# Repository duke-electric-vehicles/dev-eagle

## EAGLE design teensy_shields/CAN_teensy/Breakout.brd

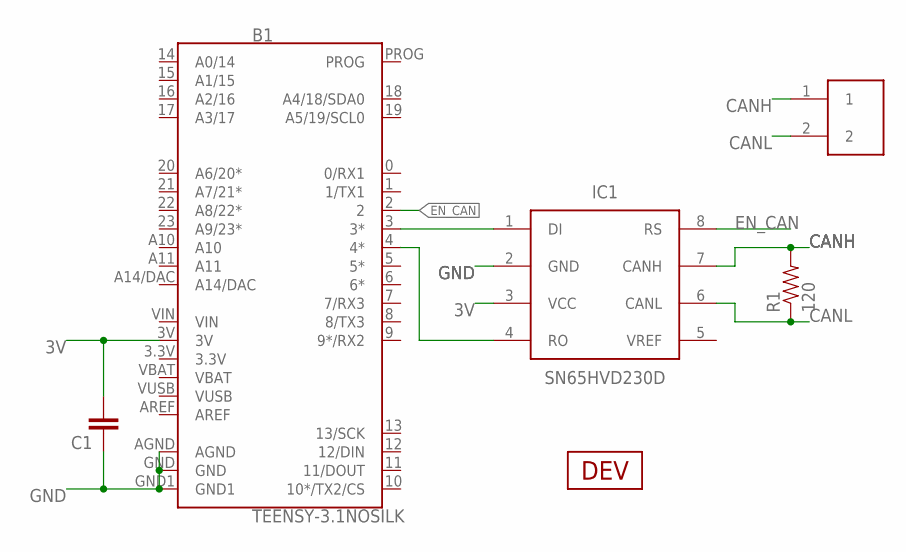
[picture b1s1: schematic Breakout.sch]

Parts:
B1: TEENSY-3.1NOSILK; TEENSY-3.1_NOSILK
C1: CAP0603-CAP; 0603-CAP
IC1: SN65HVD230D; SO-8
R1: 120; 0603-RES
U$1: HEADER2; 2PINVALULOK
U$2: DEV

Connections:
3V: B1.3.3V, B1.3V, C1.2, IC1.3 (VCC)
CANH: IC1.7 (CANH), R1.2, U$1.1
CANL: IC1.6 (CANL), R1.1, U$1.2
EN_CAN: B1.2, IC1.8 (RS)
GND: B1.AGND, B1.GND, B1.GND1, C1.1, IC1.2 (GND)
unnamed: B1.3 (3*), IC1.1 (DI)
unnamed: B1.4 (4*), IC1.4 (RO)
VBAT: B1.VBAT
VIN: B1.VIN
VUSB: B1.VUSB

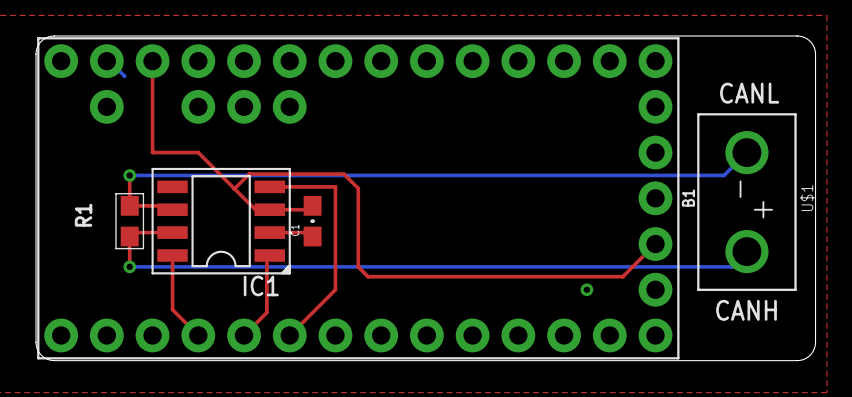
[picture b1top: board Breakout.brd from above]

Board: 2 copper layers, 43.3 x 18.0 mm, 6 parts (0 on the bottom side), 7 nets.

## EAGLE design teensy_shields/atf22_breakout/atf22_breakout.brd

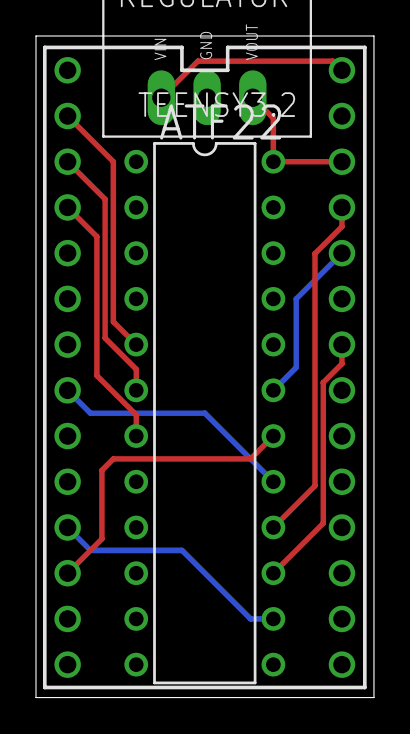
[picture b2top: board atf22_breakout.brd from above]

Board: 2 copper layers, 18.8 x 36.8 mm, 4 parts (1 on the bottom side), 12 nets.

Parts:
ATF22: ATF22; PDIP-T24
REGULATOR: V78W
TEENSY3.2: TEENSY_3.1-3.2_DIL; TEENSY_3.0-3.2&LC_DIL
U$1: DEV

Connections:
3.3V: ATF22.24, REGULATOR.OUT, TEENSY3.2.3.3V
ENC_A: ATF22.5, TEENSY3.2.0
ENC_B: ATF22.6, TEENSY3.2.1
ENC_C: ATF22.7, TEENSY3.2.2
GND: ATF22.12, REGULATOR.GND, TEENSY3.2.GND
INH_A: ATF22.14, TEENSY3.2.9
INH_B: ATF22.15, TEENSY3.2.20/A6
INH_C: ATF22.16, TEENSY3.2.23/A9
INL_A: ATF22.17, TEENSY3.2.6
INL_B: ATF22.18, TEENSY3.2.10
INL_C: ATF22.19, TEENSY3.2.22/A8
VIN: REGULATOR.IN, TEENSY3.2.VIN

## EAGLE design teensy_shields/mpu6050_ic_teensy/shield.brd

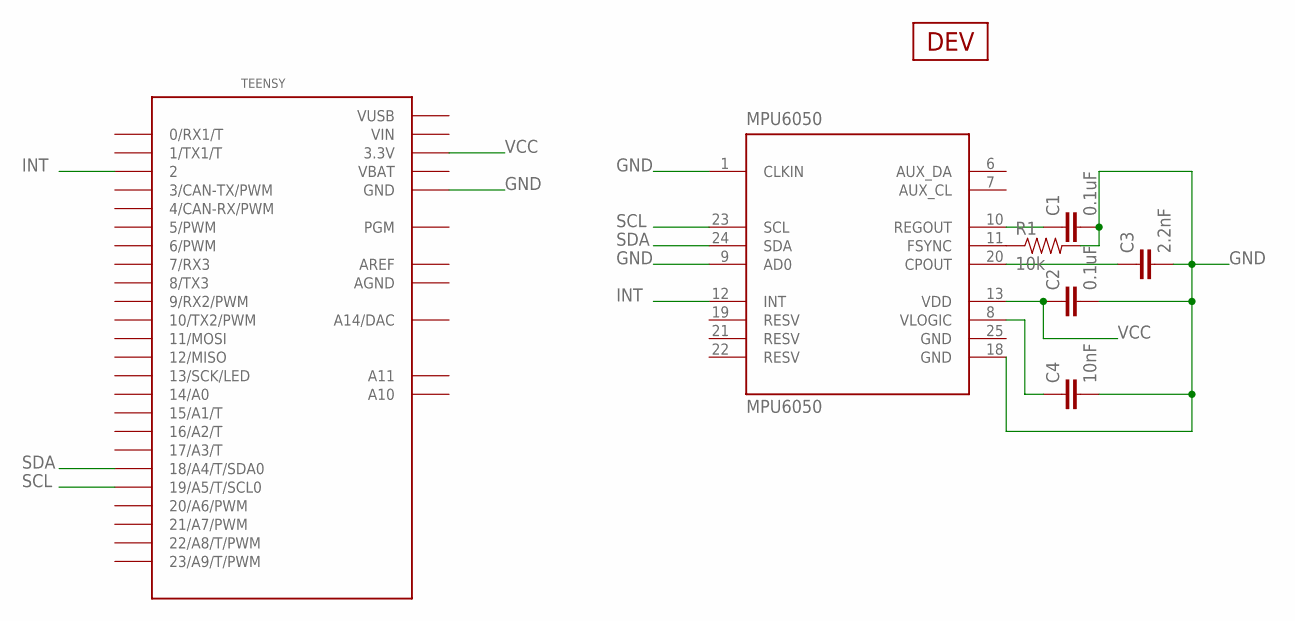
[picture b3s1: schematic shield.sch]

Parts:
C1, C2: 0.1uF; 0603-CAP
C3: 2.2nF; 0603-CAP
C4: 10nF; 0603-CAP
MPU6050: MPU6050; QFN50P400X400X95-25T265X275N
R1: 10k; 0603-RES
TEENSY: TEENSY_3.1-3.2_ALL_PINS; TEENSY_3.0-3.2&LC_ALL_PINS
U$1: DEV

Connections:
AGND: TEENSY.AGND
AREF: TEENSY.AREF
GND: C1.2, C2.2, C3.2, C4.2, MPU6050.1 (CLKIN), MPU6050.9 (AD0), MPU6050.18 (GND), MPU6050.25 (GND), R1.2, TEENSY.GND, TEENSY.GND1 (GND)
INT: MPU6050.12 (INT), TEENSY.2
unnamed: C3.1, MPU6050.20 (CPOUT)
unnamed: C1.1, MPU6050.10 (REGOUT)
unnamed: C4.1, MPU6050.8 (VLOGIC)
unnamed: MPU6050.11 (FSYNC), R1.1
SCL: MPU6050.23 (SCL), TEENSY.19/A5 (19/A5/T/SCL0)
SDA: MPU6050.24 (SDA), TEENSY.18/A4 (18/A4/T/SDA0)
VBAT: TEENSY.VBAT
VCC: C2.1, MPU6050.13 (VDD), TEENSY.3.3V, TEENSY.3.3V1 (3.3V)
VIN: TEENSY.VIN
VUSB: TEENSY.VUSB

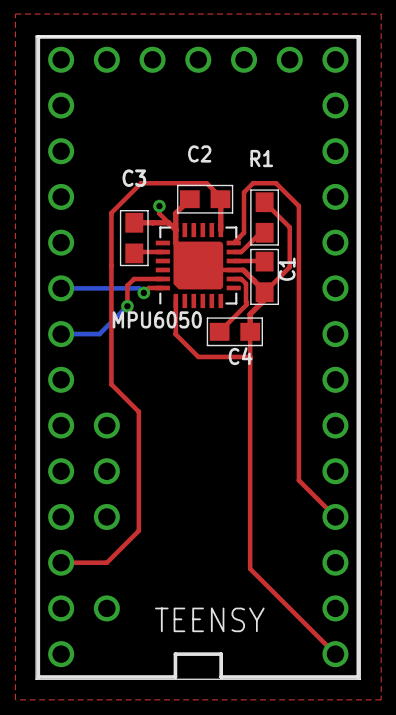
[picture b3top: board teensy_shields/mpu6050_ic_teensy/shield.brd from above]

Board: 2 copper layers, 18.0 x 35.7 mm, 8 parts (0 on the bottom side), 9 nets.

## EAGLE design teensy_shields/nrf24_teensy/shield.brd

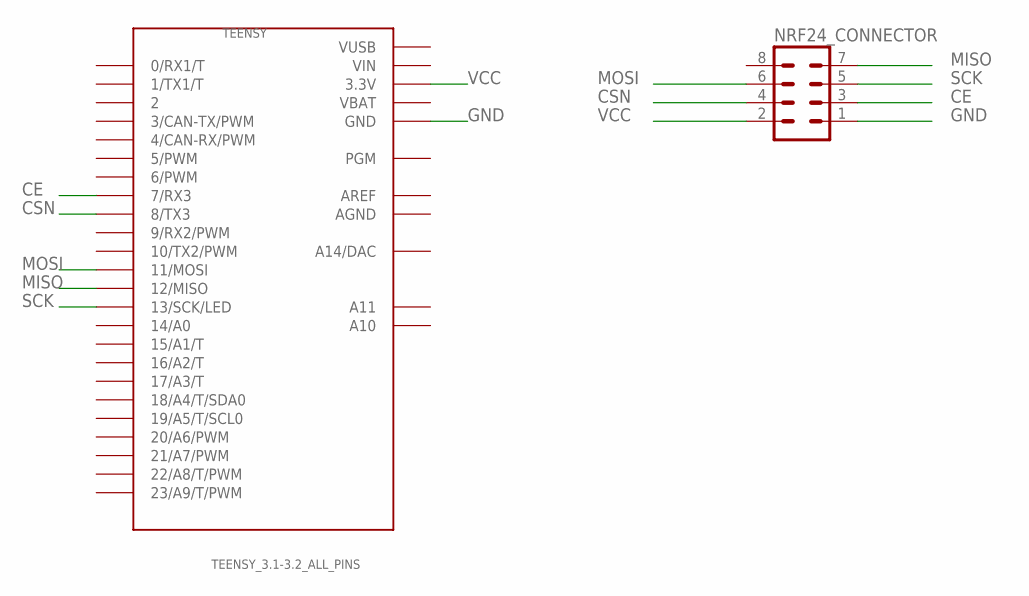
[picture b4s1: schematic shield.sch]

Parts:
NRF24_CONNECTOR: MA04-2
TEENSY: TEENSY_3.1-3.2_ALL_PINS; TEENSY_3.0-3.2&LC_ALL_PINS

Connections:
AGND: TEENSY.AGND
AREF: TEENSY.AREF
CE: NRF24_CONNECTOR.3, TEENSY.7 (7/RX3)
CSN: NRF24_CONNECTOR.4, TEENSY.8 (8/TX3)
GND: NRF24_CONNECTOR.1, TEENSY.GND, TEENSY.GND1 (GND)
MISO: NRF24_CONNECTOR.7, TEENSY.12 (12/MISO)
MOSI: NRF24_CONNECTOR.6, TEENSY.11 (11/MOSI)
SCK: NRF24_CONNECTOR.5, TEENSY.13 (13/SCK/LED)
VBAT: TEENSY.VBAT
VCC: NRF24_CONNECTOR.2, TEENSY.3.3V, TEENSY.3.3V1 (3.3V)
VIN: TEENSY.VIN
VUSB: TEENSY.VUSB

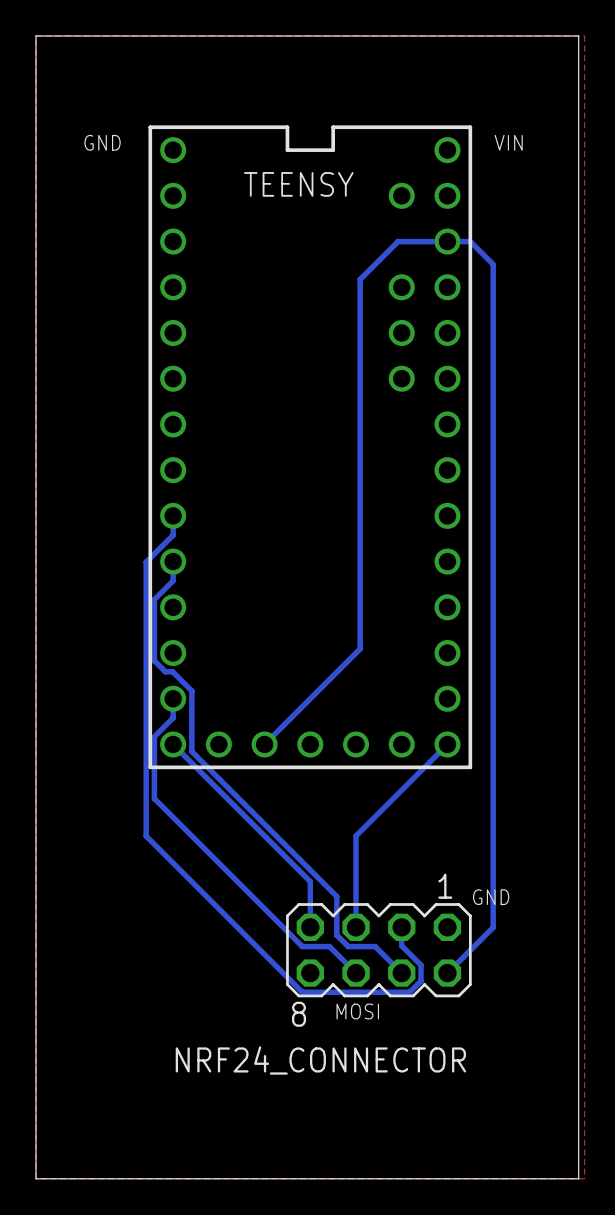
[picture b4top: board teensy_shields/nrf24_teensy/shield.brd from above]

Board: 2 copper layers, 30.2 x 63.5 mm, 3 parts (0 on the bottom side), 7 nets.

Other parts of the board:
U$1: DEV

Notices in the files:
parts and their libraries:
SparkFun-Boards: Licensing: Creative Commons ShareAlike 4.0 International - https://creativecommons.org/licenses/by-sa/4.0
